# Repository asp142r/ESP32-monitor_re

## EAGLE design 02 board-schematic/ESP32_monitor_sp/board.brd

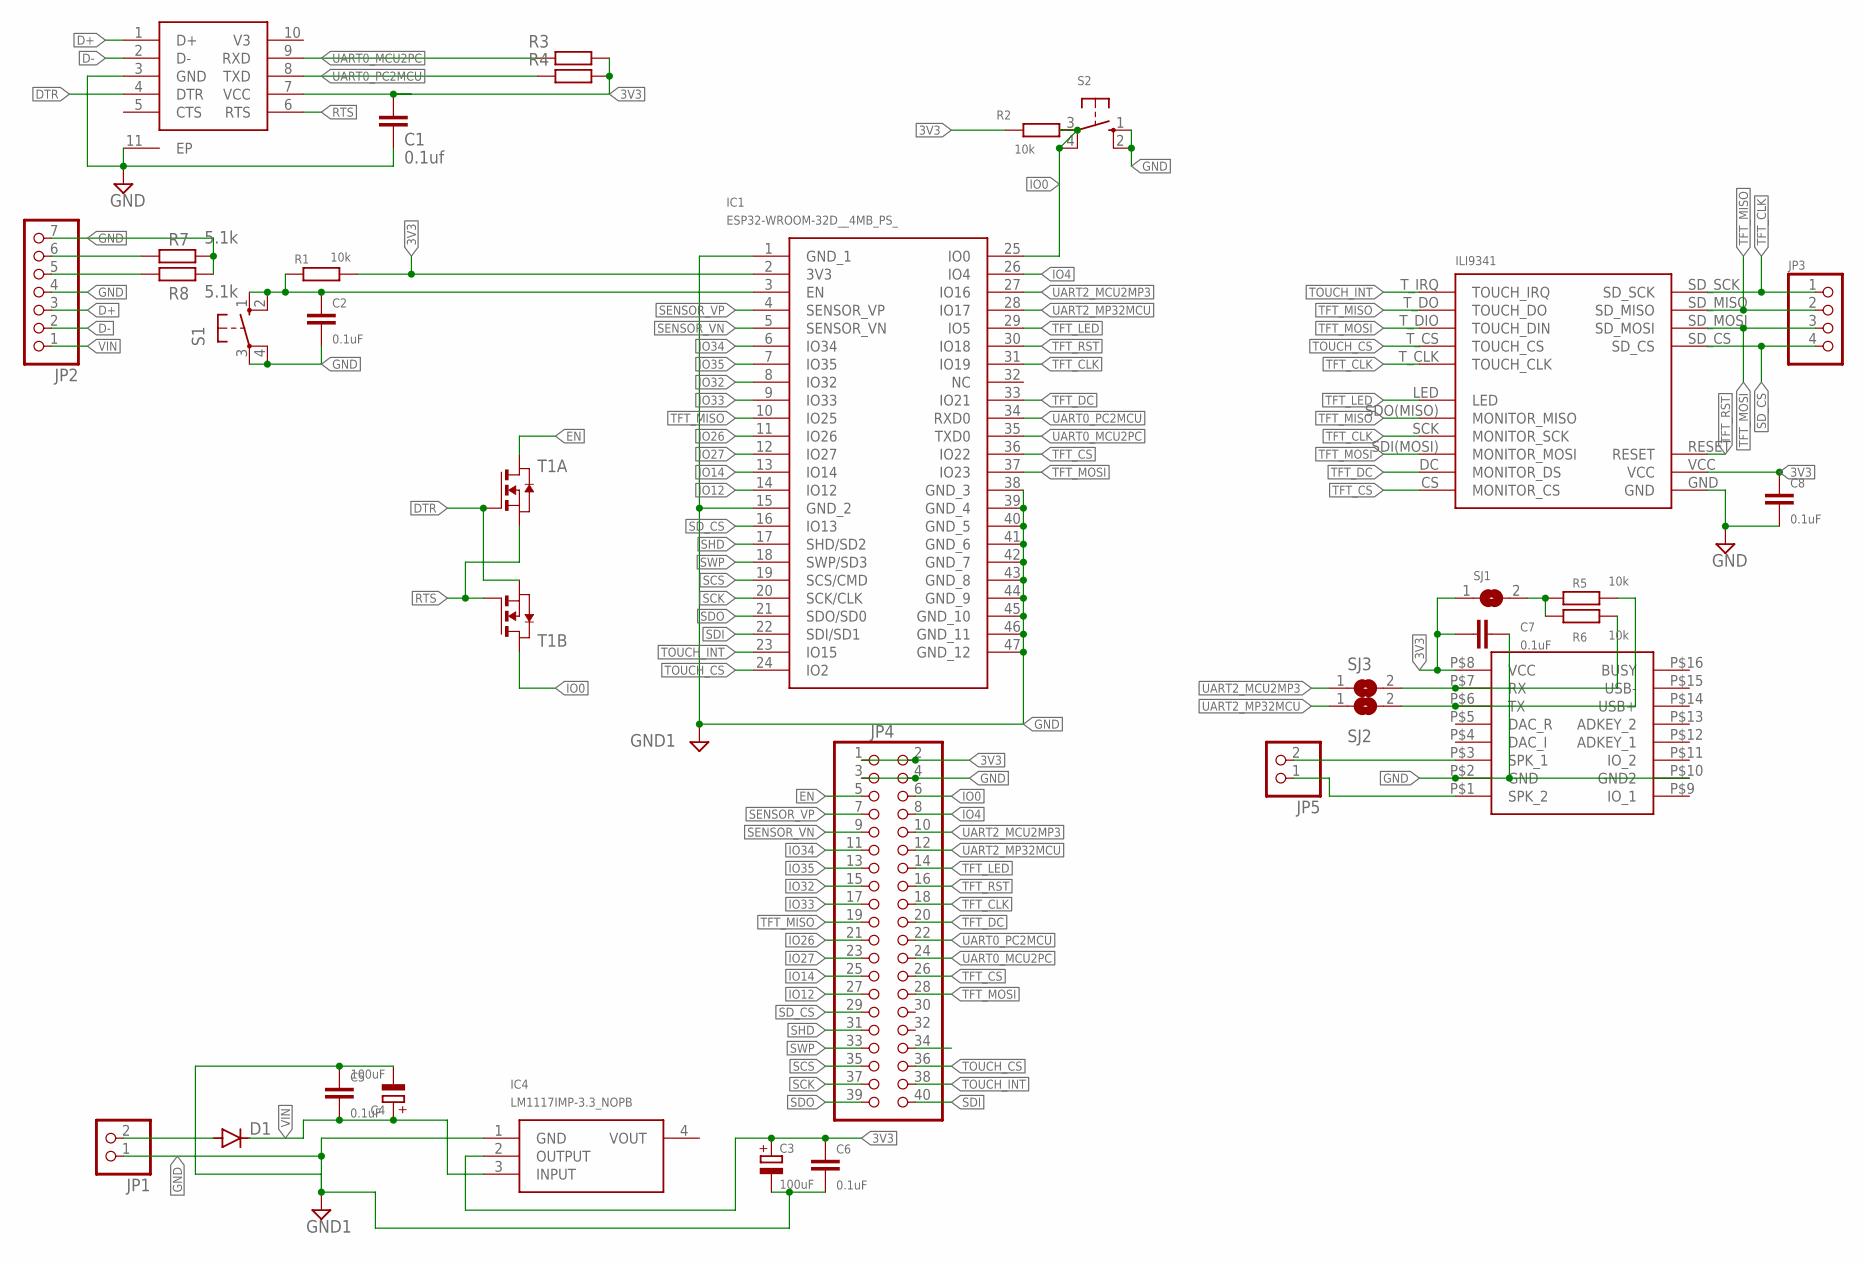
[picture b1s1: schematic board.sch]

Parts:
C1: 0.1uf; C1206
C2, C5, C6, C7, C8: 0.1uF; C1206
C3, C4: 100uF; E2,5-7
D1: DIODE-SOD123; SOD123
IC1: ESP32-WROOM-32D__4MB_PS_; ESP32WROOM32D4MBPS
IC3: CH340K; SOP100P600X150-11T240X280N
IC4: LM1117IMP-3.3_NOPB; SOT230P700X180-4N
JP1, JP5: PINHD-1X2; 1X02
JP2: PINHD-1X7; 1X07
JP3: PINHD-1X4; 1X04
JP4: PINHD-2X20; 2X20
R1, R2, R5, R6: 10k; M1206
R3, R4: R-EU_M1206; M1206
R7, R8: 5.1k; M1206
S1, S2: 10-XX; B3F-10XX
SJ1, SJ2, SJ3: SJ
T1: NMOS2SO8; SO8
U$1: ILI9341_MODULE1
U$2: DFPLAYER_MINI

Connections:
3V3: C1.1, C3.+, C6.1, C7.1, C8.1, IC1.2 (3V3), IC3.7 (VCC), IC4.2 (OUTPUT), JP4.1, JP4.2, R1.2, R2.1, R3.2, R4.2, SJ1.1, U$1.VCC, U$2.P$8 (VCC)
D+: IC3.1 (D+), JP2.3
D-: IC3.2 (D-), JP2.2
DTR: IC3.4 (DTR), T1.2 (G), T1.3 (S)
EN: C2.1, IC1.3 (EN), JP4.5, R1.1, S1.1 (S), S1.2 (S1), T1.7 (D), T1.8 (D)
GND: C1.2, C2.2, C3.-, C4.-, C5.1, C6.2, C7.2, C8.2, IC1.1 (GND_1), IC1.15 (GND_2), IC1.38 (GND_3), IC1.39 (GND_4), IC1.40 (GND_5), IC1.41 (GND_6), IC1.42 (GND_7), IC1.43 (GND_8), IC1.44 (GND_9), IC1.45 (GND_10), IC1.46 (GND_11), IC1.47 (GND_12), IC3.3 (GND), IC3.11 (EP), IC4.1 (GND), JP1.1, JP2.4, JP2.7, JP4.3, JP4.4, R7.2, R8.2, S1.3, S1.4 (P1), S2.1 (S), S2.2 (S1), U$1.GND, U$2.P$2 (GND), U$2.P$10 (GND2)
IO0: IC1.25 (IO0), JP4.6, JP4.34, R2.2, S2.3, S2.4 (P1), T1.5 (D), T1.6 (D)
IO4: IC1.26 (IO4), JP4.8
IO12: IC1.14 (IO12), JP4.27
IO14: IC1.13 (IO14), JP4.25
IO26: IC1.11 (IO26), JP4.21
IO27: IC1.12 (IO27), JP4.23
IO32: IC1.8 (IO32), JP4.15
IO33: IC1.9 (IO33), JP4.17
IO34: IC1.6 (IO34), JP4.11
IO35: IC1.7 (IO35), JP4.13
MP3_RX: R6.2, SJ3.2, U$2.P$7 (RX)
MP3_TX: R5.2, SJ2.2, U$2.P$6 (TX)
unnamed: JP5.2, U$2.P$3 (SPK_1)
unnamed: D1.A, JP1.2
unnamed: JP2.6, R7.1
unnamed: JP2.5, R8.1
unnamed: R5.1, R6.1, SJ1.2
RTS: IC3.6 (RTS), T1.1 (S), T1.4 (G)
SCK: IC1.20 (SCK/CLK), JP4.37
SCS: IC1.19 (SCS/CMD), JP4.35
SDI: IC1.22 (SDI/SD1), JP4.40
SDO: IC1.21 (SDO/SD0), JP4.39
SD_CS: IC1.16 (IO13), JP3.4, JP4.29, U$1.SD_CS
SENSOR_VN: IC1.5 (SENSOR_VN), JP4.9
SENSOR_VP: IC1.4 (SENSOR_VP), JP4.7
SHD: IC1.17 (SHD/SD2), JP4.31
SPK2: JP5.1, U$2.P$1 (SPK_2)
SWP: IC1.18 (SWP/SD3), JP4.33
TFT_CLK: IC1.31 (IO19), JP3.1, JP4.18, U$1.SCK (MONITOR_SCK), U$1.SD_SCK, U$1.T_CLK (TOUCH_CLK)
TFT_CS: IC1.36 (IO22), JP4.26, U$1.CS (MONITOR_CS)
TFT_DC: IC1.33 (IO21), JP4.20, U$1.DC (MONITOR_DS)
TFT_LED: IC1.29 (IO5), JP4.14, U$1.LED
TFT_MISO: IC1.10 (IO25), JP3.2, JP4.19, U$1.SDO(MISO) (MONITOR_MISO), U$1.SD_MISO, U$1.T_DO (TOUCH_DO)
TFT_MOSI: IC1.37 (IO23), JP3.3, JP4.28, U$1.SDI(MOSI) (MONITOR_MOSI), U$1.SD_MOSI, U$1.T_DIO (TOUCH_DIN)
TFT_RST: IC1.30 (IO18), JP4.16, U$1.RESET
TOUCH_CS: IC1.24 (IO2), JP4.36, U$1.T_CS (TOUCH_CS)
TOUCH_INT: IC1.23 (IO15), JP4.38, U$1.T_IRQ (TOUCH_IRQ)
UART0_MCU2PC: IC1.35 (TXD0), IC3.9 (RXD), JP4.24, R3.1
UART0_PC2MCU: IC1.34 (RXD0), IC3.8 (TXD), JP4.22, R4.1
UART2_MCU2MP3: IC1.27 (IO16), JP4.10, SJ3.1
UART2_MP32MCU: IC1.28 (IO17), JP4.12, SJ2.1
VIN: C4.+, C5.2, D1.C, IC4.3 (INPUT), JP2.1

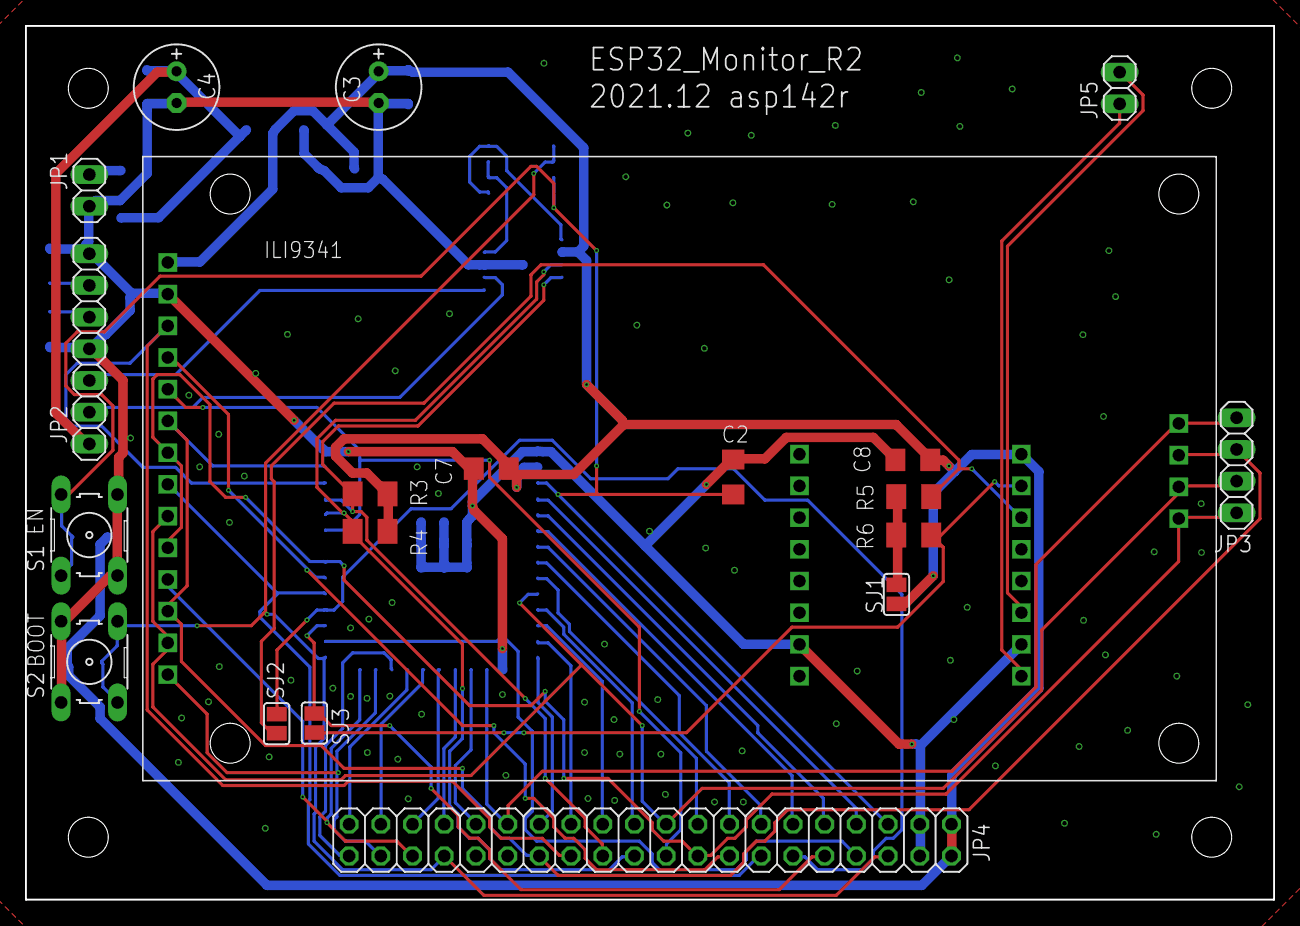
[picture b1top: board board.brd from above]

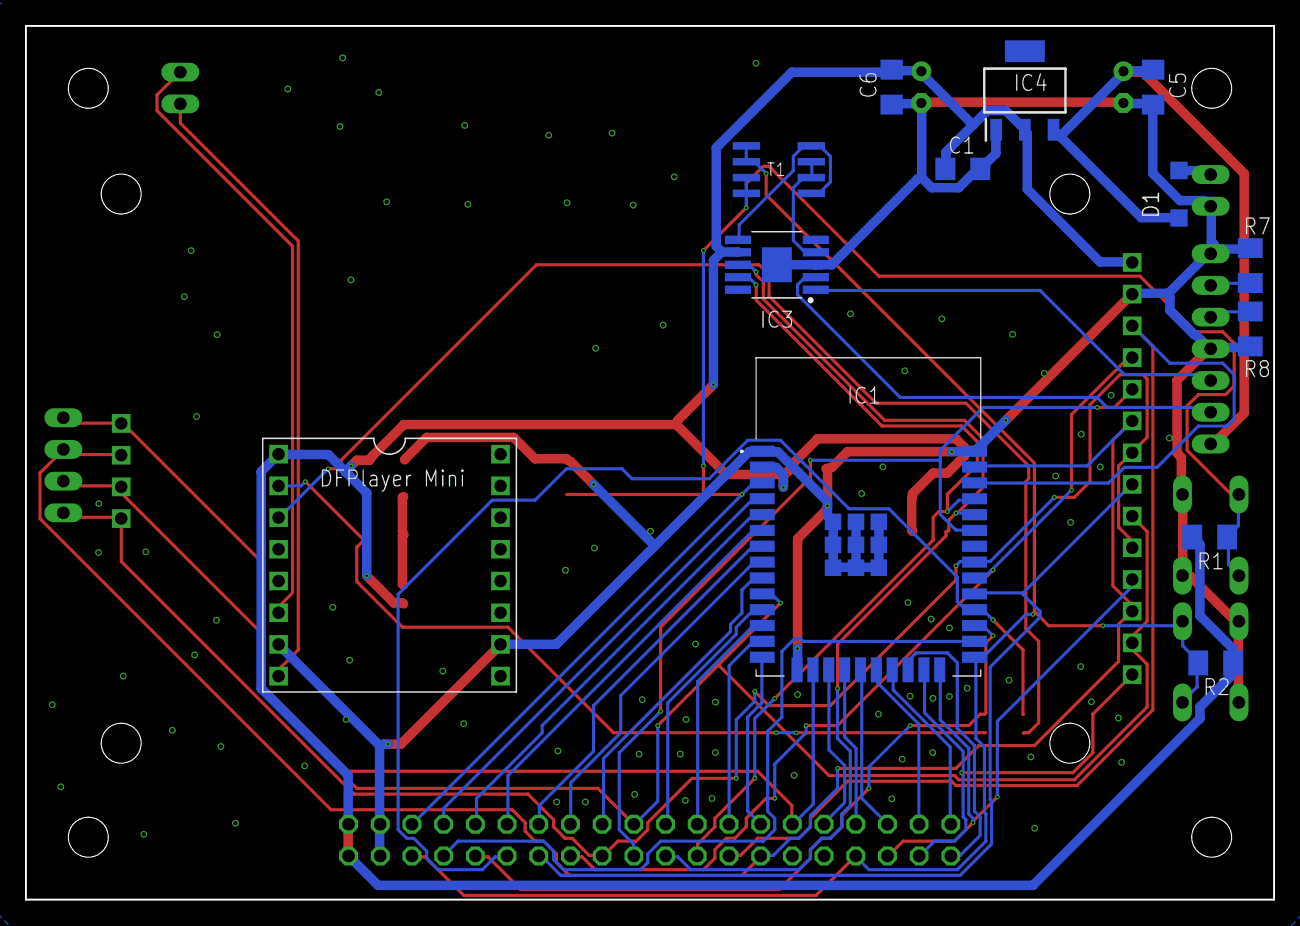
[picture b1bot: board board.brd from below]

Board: 2 copper layers, 100.0 x 70.0 mm, 33 parts (13 on the bottom side), 48 nets.

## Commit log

2022-01-08 first
2022-01-08 Update Board
